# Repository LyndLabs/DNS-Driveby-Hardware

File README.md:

# DNS-Driveby-Hardware

## PCB Dimensions
76x40mm, 3mm radius

## v1.3 Changelog
- Flip SH1106 Screen Polarity 
- Moved Screen Over D1 Mini
- Flip LiPo Battery Polarity (Adafruit Standard)
- External Antenna
- MicroSD Card Breakout
- Fix Swapped GPS UART Traces
- GPS High-Side Switching
- Silkscreen Updates

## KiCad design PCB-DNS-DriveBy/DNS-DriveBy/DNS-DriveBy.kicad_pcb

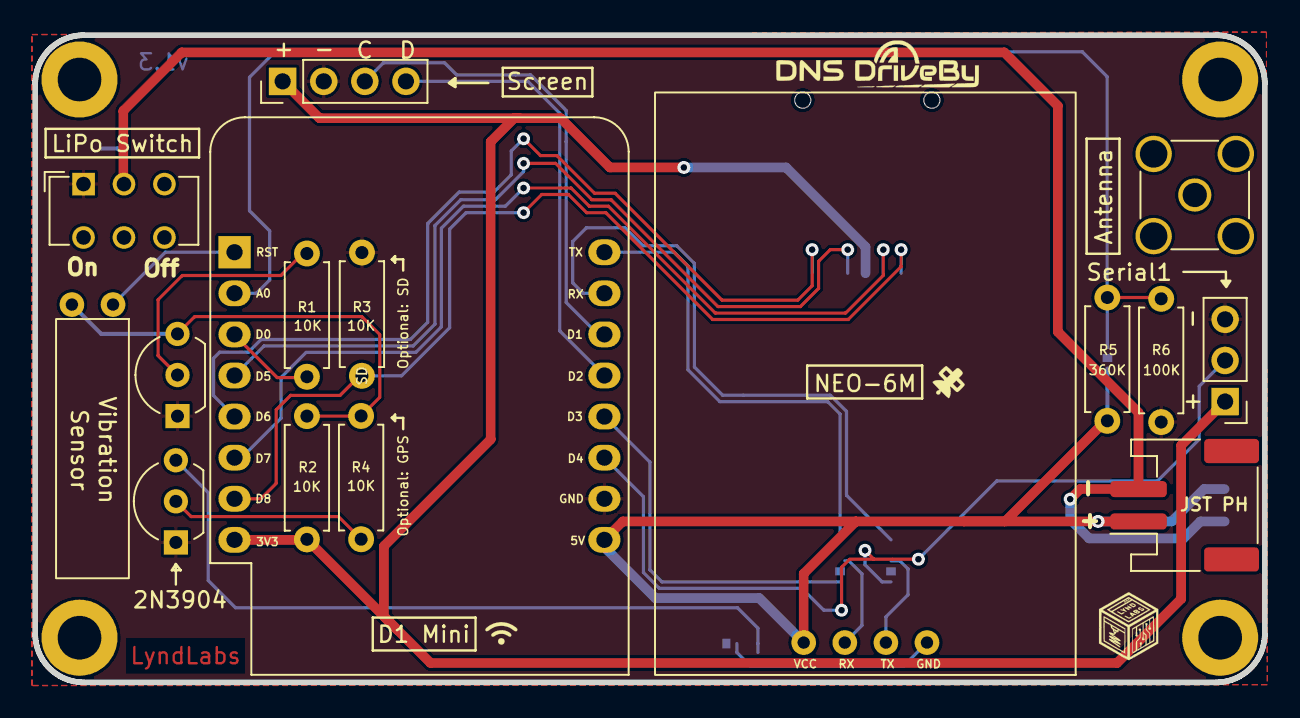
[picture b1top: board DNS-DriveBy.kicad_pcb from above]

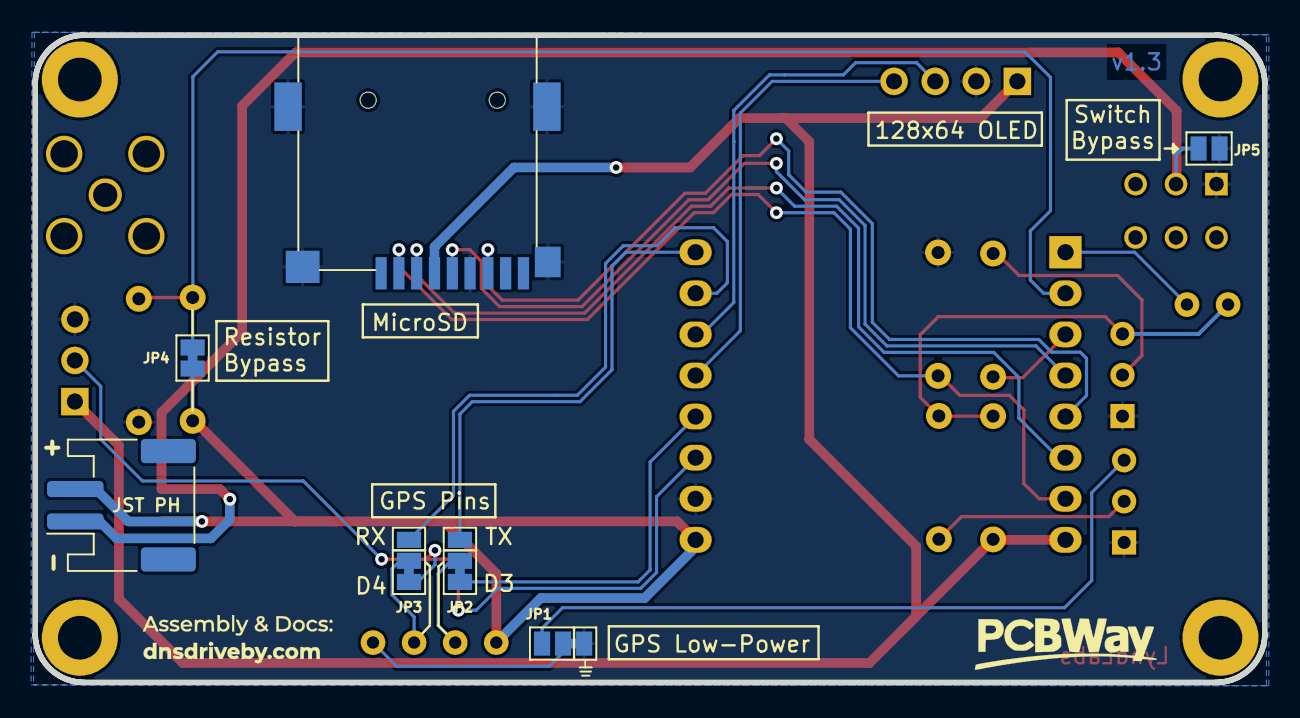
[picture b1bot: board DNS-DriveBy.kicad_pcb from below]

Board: 2 copper layers, 76.0 x 40.0 mm, 24 parts (7 on the bottom side), 23 nets.

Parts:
Antenna: SMA Antenna; SMA_Amphenol_901-144_Vertical
J1, J1#2: JST 2.0; JST_PH_S2B-PH-SM4-TB_1x02-1MP_P2.00mm_Horizontal
J2: SH1106; PinHeader_1x04_P2.54mm_Vertical
J3: Conn_01x03; PinHeader_1x03_P2.54mm_Vertical
J4: Micro_SD_Card_Det; MicroSD
JP1, JP2, JP3: SolderJumper_3_Bridged12; SolderJumper-3_P1.3mm_Bridged12_Pad1.0x1.5mm
JP4: Jumper_2_Bridged; SolderJumper-2_P1.3mm_Bridged_Pad1.0x1.5mm
JP5: Jumper_2_Open; SolderJumper-2_P1.3mm_Open_Pad1.0x1.5mm
Q1, Q2: 2N3904; TO-92L_Inline_Wide
R1, R2, R3, R4: 10K; R_Axial_DIN0207_L6.3mm_D2.5mm_P7.62mm_Horizontal
R5: 360K; R_Axial_DIN0207_L6.3mm_D2.5mm_P7.62mm_Horizontal
R6: 100K; R_Axial_DIN0207_L6.3mm_D2.5mm_P7.62mm_Horizontal
Ref**: Val**; v1.0-pcb-art
S1: Vibration; Vibration Sensor
SW1: SW_SPST; SW_CuK_JS202011CQN_DPDT_Straight
U1: D1 Mini; WEMOS_D1_mini_light
U2: NEO-6M; NEO-6M GPS

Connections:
+3V3: J2.1, J3.1, J4.4 (VDD), R2.2, U1.8 (3V3)
+BATT: J1.1, J1#2.2, JP4.1 (A), R5.1, U1.9 (5V), U2.1 (VCC)
A0: JP4.2 (B), R5.2, R6.1, U1.2 (A0)
D0: R1.1, U1.3 (D0)
D3: JP2.1 (A), U1.12 (D3)
D4: J3.2, JP3.1 (A), U1.11 (D4)
GND: J2.2, J3.3, J4.6 (VSS), J4.11 (SHIELD), JP1.1 (A), JP5.1 (A), Q1.1 (E), Q2.1 (E), R3.2, R6.2, SW1.1 (A), U1.10 (GND)
GPS-EN: Q1.3 (C), R2.1, R4.2
GPS_RX: JP2.3 (B), U1.16 (TX)
GPS_TX: JP3.3 (B), U1.15 (RX)
MISO: J4.7 (DAT0), U1.5 (MISO/D6)
MOSI: J4.3 (CMD), U1.6 (MOSI/D7)
unnamed: J1.2, J1#2.1, JP5.2 (B), SW1.2 (B)
unnamed: JP1.3 (B), Q2.3 (C)
unnamed: JP2.2 (C), U2.2 (RX)
unnamed: JP3.2 (C), U2.3 (TX)
unnamed: Q1.2 (B), R1.2
unnamed: Q2.2 (B), R4.1
unnamed: JP1.2 (C), U2.4 (GND)
SCK: J4.5 (CLK), U1.4 (SCK/D5)
SCL: J2.3, U1.14 (SCL/D1)
SDA: J2.4, U1.13 (SDA/D2)
SS: J4.2 (DAT3/CD), R3.1, U1.7 (CS/D8)

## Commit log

2023-07-02 publish PCB & enclosure design files for v1.2 kit
2023-07-20 publish v1.3 design files
2023-07-20 publish changelog
2023-07-22 update jumper pad position
2023-10-05 push full enclosure
2023-12-03 Create folder
2023-12-03 upload 3d printed case files
2023-12-03 Delete Cases/r3dfish/test.removeme
    this file was only needed to create the directory on github
